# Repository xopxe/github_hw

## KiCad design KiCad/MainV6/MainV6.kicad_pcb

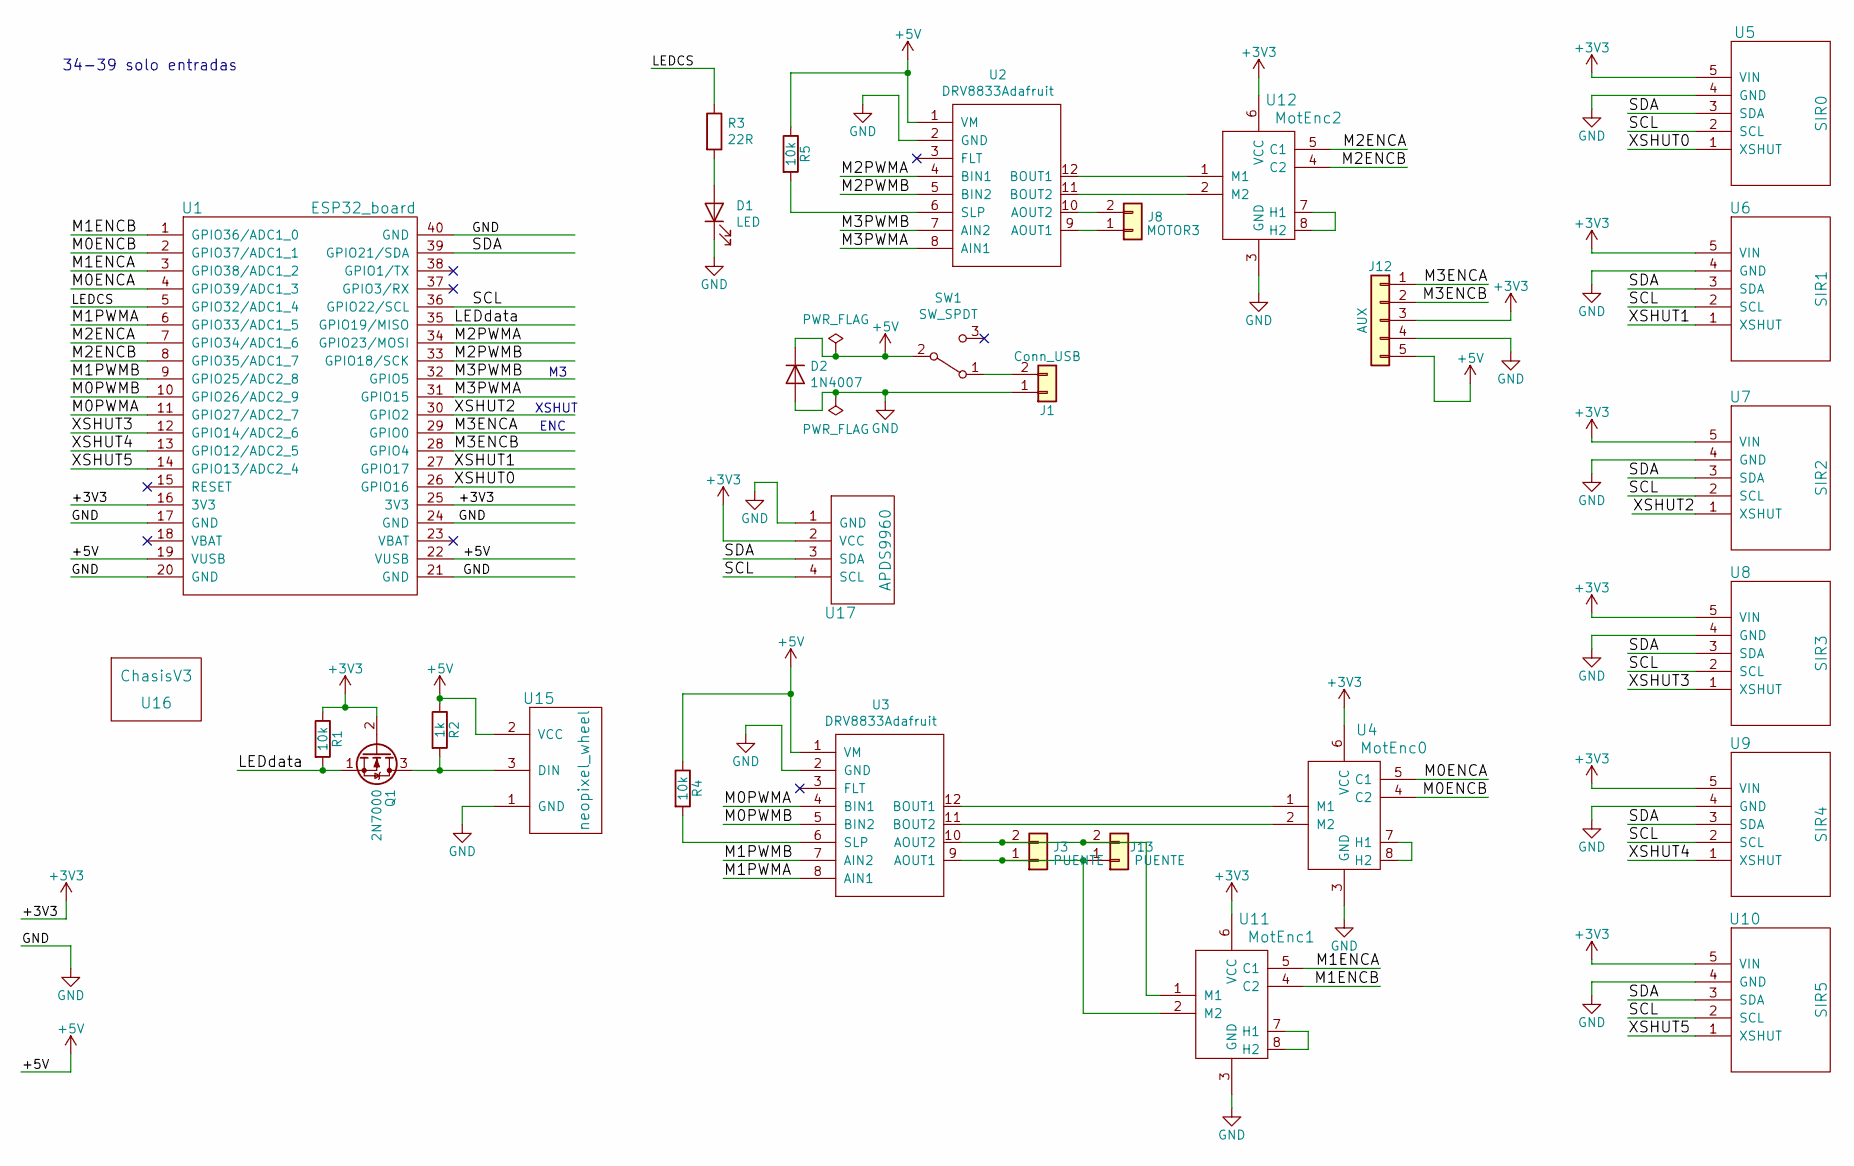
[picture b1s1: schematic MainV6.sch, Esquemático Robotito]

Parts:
D1: LED; LED_0805
D2: 1N4007; D_DO-41_SOD81_P10.16mm_Horizontal
J1: Conn_USB; PhoenixContact_MCV_1,5_2-G-3.81_1x02_P3.81mm_Vertical; MPN OSTTA024163
J3, J13: PUENTE; PinHeader_1x02_P2.54mm_Vertical
J8: MOTOR3; JST_XH_B02B-XH-A_1x02_P2.50mm_Vertical
J12: AUX; AUX_PINS
Q1: 2N7000; TO-92_Molded_Narrow; MPN 2N7000
R1, R5: 10k; R_Axial_DIN0204_L3.6mm_D1.6mm_P7.62mm_Horizontal; MPN RNF14FTD10K0
R2: 1k; R_Axial_DIN0204_L3.6mm_D1.6mm_P7.62mm_Horizontal; MPN RNF14FTD10K0
R3: 22R; R_Axial_DIN0204_L3.6mm_D1.6mm_P7.62mm_Horizontal
R4: 10k; R_Axial_DIN0309_L9.0mm_D3.2mm_P12.70mm_Horizontal; MPN RNF14FTD10K0
SW1: SW_SPDT; SlideSwitchFP_V2
U1: ESP32_board; ESP32_phV2; MPN DEV-13907
U2, U3: DRV8833Adafruit; DRV8833_phMinV2
U4: MotEnc0; MotorCompletoFP
U5: SIR0; ToFSensor_FP; MPN 640455-6
U6: SIR1; ToFSensor_FP; MPN 640455-6
U7: SIR2; ToFSensor_FP; MPN 640455-6
U8: SIR3; ToFSensor_FP; MPN 640455-6
U9: SIR4; ToFSensor_FP; MPN 640455-6
U10: SIR5; ToFSensor_FP; MPN 640455-6
U11: MotEnc1; MotorCompletoFP
U12: MotEnc2; MotorCompletoFP
U15: neopixel_wheel; Pin_Header_Straight_1x03_Pitch2.54mm; MPN 61300311121
U16: ChasisV3; ChasisV6
U17: APDS9960; ColorSensorPHV4; MPN TSM-106-02-T-SV

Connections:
+3V3: J12.3, Q1.2 (G), R1.1, U1.16 (3V3), U1.25 (3V3), U4.6 (VCC), U5.5 (VIN), U6.5 (VIN), U7.5 (VIN), U8.5 (VIN), U9.5 (VIN), U10.5 (VIN), U11.6 (VCC), U12.6 (VCC), U17.2 (VCC)
+5V: D2.1 (K), J12.5, R2.1, R4.1, R5.1, SW1.2 (B), U1.19 (VUSB), U1.22 (VUSB), U2.1 (VM), U3.1 (VM), U15.2 (VCC)
/LEDCS: R3.1, U1.5 (GPIO32/ADC1_4)
/LEDdata: Q1.1 (S), R1.2, U1.35 (GPIO19/MISO)
/M0ENCA: U1.4 (GPIO39/ADC1_3), U4.5 (C1)
/M0ENCB: U1.2 (GPIO37/ADC1_1), U4.4 (C2)
/M0PWMA: U1.11 (GPIO27/ADC2_7), U3.4 (BIN1)
/M0PWMB: U1.10 (GPIO26/ADC2_9), U3.5 (BIN2)
/M1ENCA: U1.3 (GPIO38/ADC1_2), U11.5 (C1)
/M1ENCB: U1.1 (GPIO36/ADC1_0), U11.4 (C2)
/M1PWMA: U1.6 (GPIO33/ADC1_5), U3.8 (AIN1)
/M1PWMB: U1.9 (GPIO25/ADC2_8), U3.7 (AIN2)
/M2ENCA: U1.7 (GPIO34/ADC1_6), U12.5 (C1)
/M2ENCB: U1.8 (GPIO35/ADC1_7), U12.4 (C2)
/M2PWMA: U1.34 (GPIO23/MOSI), U2.4 (BIN1)
/M2PWMB: U1.33 (GPIO18/SCK), U2.5 (BIN2)
/M3ENCA: J12.1, U1.29 (GPIO0)
/M3ENCB: J12.2, U1.28 (GPIO4)
/M3PWMA: U1.31 (GPIO15), U2.8 (AIN1)
/M3PWMB: U1.32 (GPIO5), U2.7 (AIN2)
/SCL: U1.36 (GPIO22/SCL), U5.2 (SCL), U6.2 (SCL), U7.2 (SCL), U8.2 (SCL), U9.2 (SCL), U10.2 (SCL), U17.4 (SCL)
/SDA: U1.39 (GPIO21/SDA), U5.3 (SDA), U6.3 (SDA), U7.3 (SDA), U8.3 (SDA), U9.3 (SDA), U10.3 (SDA), U17.3 (SDA)
/XSHUT0: U1.26 (GPIO16), U5.1 (XSHUT)
/XSHUT1: U1.27 (GPIO17), U6.1 (XSHUT)
/XSHUT2: U1.30 (GPIO2), U7.1 (XSHUT)
/XSHUT3: U1.12 (GPIO14/ADC2_6), U8.1 (XSHUT)
/XSHUT4: U1.13 (GPIO12/ADC2_5), U9.1 (XSHUT)
/XSHUT5: U1.14 (GPIO13/ADC2_4), U10.1 (XSHUT)
GND: D1.1 (K), D2.2 (A), J1.1, J12.4, U1.17 (GND), U1.20 (GND), U1.21 (GND), U1.24 (GND), U1.40 (GND), U2.2 (GND), U3.2 (GND), U4.3 (GND), U5.4 (GND), U6.4 (GND), U7.4 (GND), U8.4 (GND), U9.4 (GND), U10.4 (GND), U11.3 (GND), U12.3 (GND), U15.1 (GND), U17.1 (GND)
unnamed: D1.2 (A), R3.2
unnamed: J1.2, SW1.1 (A)
unnamed: J8.1, U2.9 (AOUT1)
unnamed: J8.2, U2.10 (AOUT2)
unnamed: J3.1, J13.1, U3.9 (AOUT1), U11.2 (M2)
unnamed: J3.2, J13.2, U3.10 (AOUT2), U11.1 (M1)
unnamed: Q1.3 (D), R2.2, U15.3 (DIN)
unnamed: R4.2, U3.6 (SLP)
unnamed: R5.2, U2.6 (SLP)
unnamed: U3.11 (BOUT2), U4.2 (M2)
unnamed: U3.12 (BOUT1), U4.1 (M1)
unnamed: U4.7 (H1), U4.8 (H2)
unnamed: U11.7 (H1), U11.8 (H2)
unnamed: U2.12 (BOUT1), U12.1 (M1)
unnamed: U2.11 (BOUT2), U12.2 (M2)
unnamed: U12.7 (H1), U12.8 (H2)

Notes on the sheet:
34-39 solo entradas
XSHUT
ENC

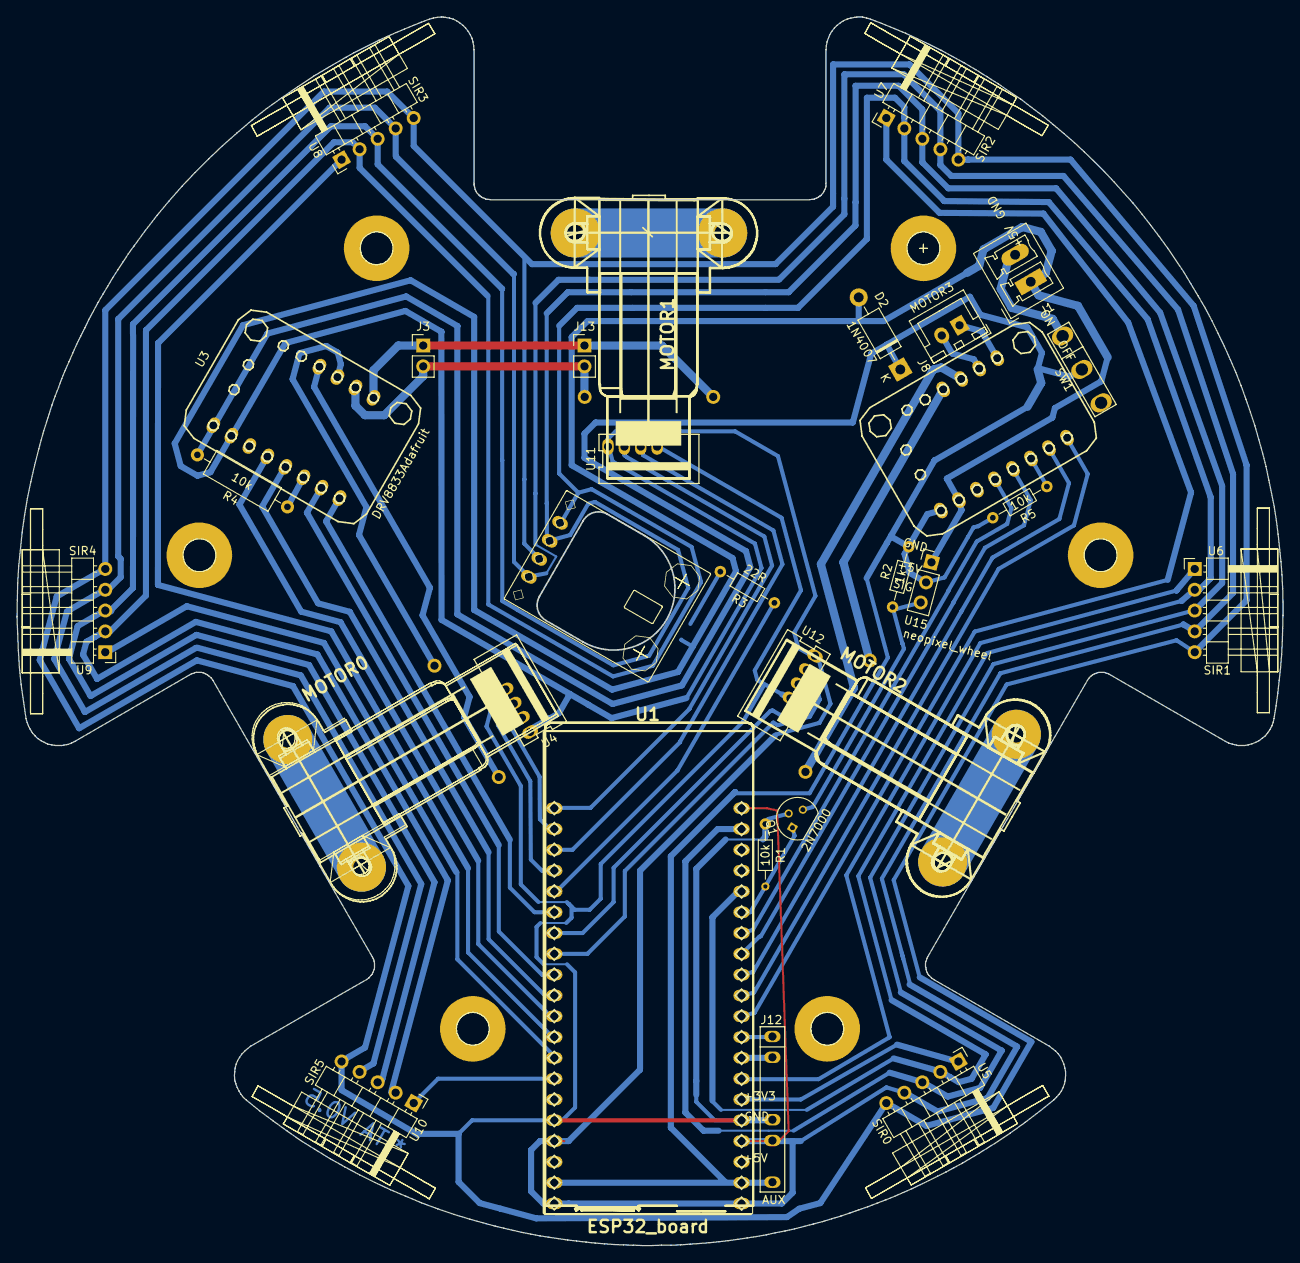
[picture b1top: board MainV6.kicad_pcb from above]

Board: 2 copper layers, 154.6 x 150.0 mm, 29 parts (1 on the bottom side), 45 nets.

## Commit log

2018-10-16 add README
2019-01-15 Agregado de versión 5.
2019-01-15 Agregado de archivos
2019-01-15 Agregado de huellas
2019-01-15 Agregado de versión 6
2019-04-08 Add LICENSE
2019-04-08 Update LICENSE
